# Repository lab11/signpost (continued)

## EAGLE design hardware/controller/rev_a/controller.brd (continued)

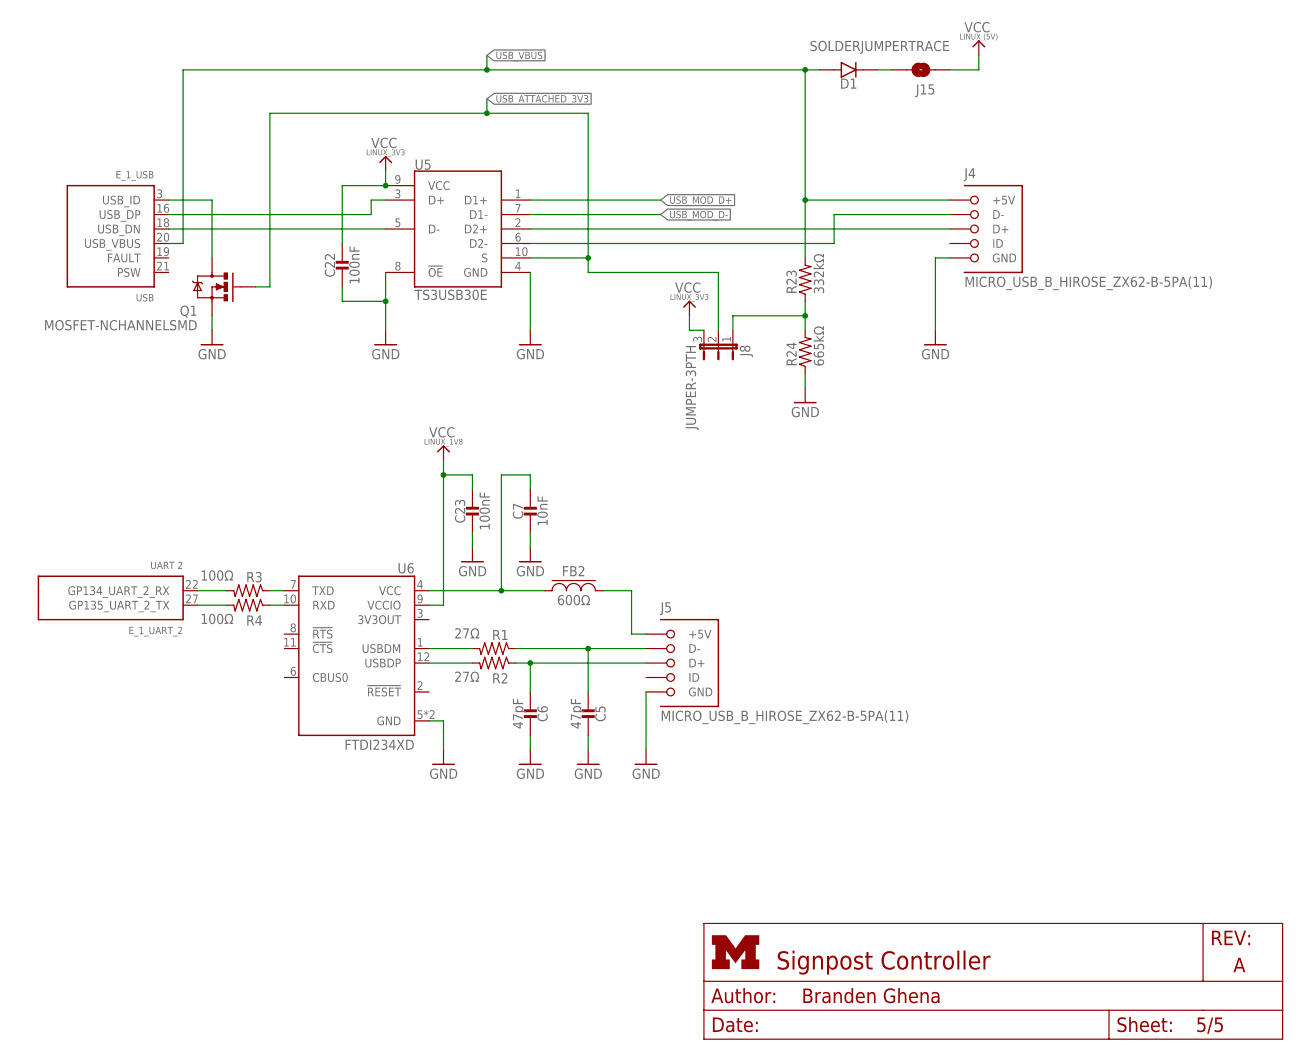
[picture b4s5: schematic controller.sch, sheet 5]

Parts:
C5, C6: 47pF; 0402_CAP; DIGIKEY 490-6241-1-ND
C7: 10nF; 0402_CAP; DIGIKEY 490-6296-1-ND
C22, C23: 100nF; 0402_CAP; DIGIKEY 490-10777-1-ND
D1: DIODE; 0402_DIODE; DIGIKEY P18981CT-ND
E_1: EDISON_CONNECTOR_SEGMENTED; EDISON_DAUGHTER; MOUSER 798-DF40HC3070DS4V51
FB2: 600Ω; 0805_CAP; DIGIKEY 240-2390-1-ND
J4, J5: MICRO_USB_B_HIROSE_ZX62-B-5PA(11); USB_MICRO_B-HIROSE-ZX62-B-5PA(11)
J8: JUMPER-3PTH; 1X03
J15: SOLDERJUMPERTRACE; SJ_2S-TRACE
Q1: MOSFET-NCHANNELSMD; SOT23-3; DIGIKEY SI2312CDS-T1-GE3CT-ND
R1, R2: 27Ω; 0402_RES; DIGIKEY 1276-3907-1-ND
R3, R4: 100Ω; 0402_RES; DIGIKEY 1276-3429-1-ND
R23: 332kΩ; 0402_RES; DIGIKEY 1276-4245-1-ND
R24: 665kΩ; 0402_RES; DIGIKEY 1276-4275-1-ND
U5: TS3USB30E; UQFN-10
U6: FTDI234XD; DFN-12/3MM

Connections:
D+: C6.1, J5.3 (D+), R2.1
D-: C5.1, J5.2 (D-), R1.1
EDISON_UART_RX: E_1.22 (GP134_UART_2_RX), R3.2
EDISON_UART_TX: E_1.27 (GP135_UART_2_TX), R4.2
GND: C5.2, C6.2, C7.2, C22.2, C23.2, J4.5 (GND), J5.5 (GND), Q1.2 (S), R24.1, U5.4 (GND), U5.8 (!OE), U6.5 (GND), U6.13 (GND); also elsewhere on the board
unnamed: R1.2, U6.1 (USBDM)
unnamed: R2.2, U6.12 (USBDP)
unnamed: J4.2 (D-), U5.6 (D2-)
unnamed: J4.3 (D+), U5.2 (D2+)
unnamed: FB2.P$2, J5.1 (+5V)
unnamed: D1.CATHODE, J15.2
unnamed: J8.1, R23.1, R24.2
unnamed: R3.1, U6.7 (TXD)
unnamed: R4.1, U6.10 (RXD)
unnamed: C7.1, FB2.P$1, U6.4 (VCC)
unnamed: E_1.3 (USB_ID), Q1.3 (D)
USB_ATTACHED_3V3: J8.2, Q1.1 (G), U5.10 (S)
USB_D+: E_1.16 (USB_DP), U5.3 (D+)
USB_D-: E_1.18 (USB_DN), U5.5 (D-)
USB_MOD_D+: U5.1 (D1+); also elsewhere on the board
USB_MOD_D-: U5.7 (D1-); also elsewhere on the board
USB_VBUS: D1.ANODE, E_1.20 (USB_VBUS), J4.1 (+5V), R23.2
VCC_LINUX: J15.1; also elsewhere on the board
VCC_LINUX_1V8: C23.1, U6.9 (VCCIO); also elsewhere on the board
VCC_LINUX_3V3: C22.1, J8.3, U5.9 (VCC); also elsewhere on the board

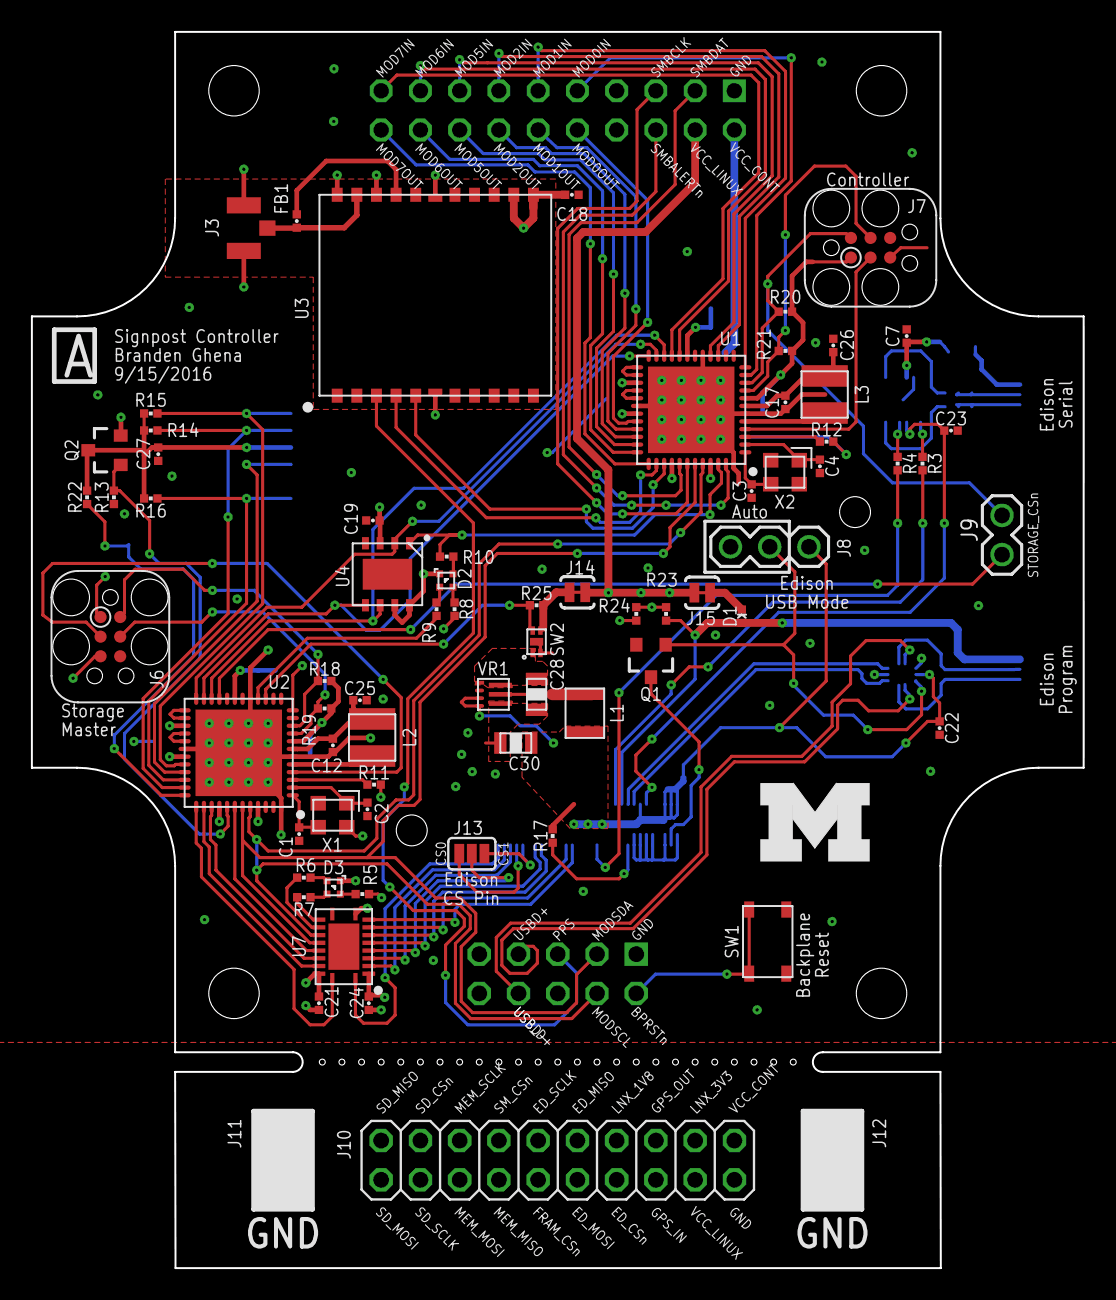
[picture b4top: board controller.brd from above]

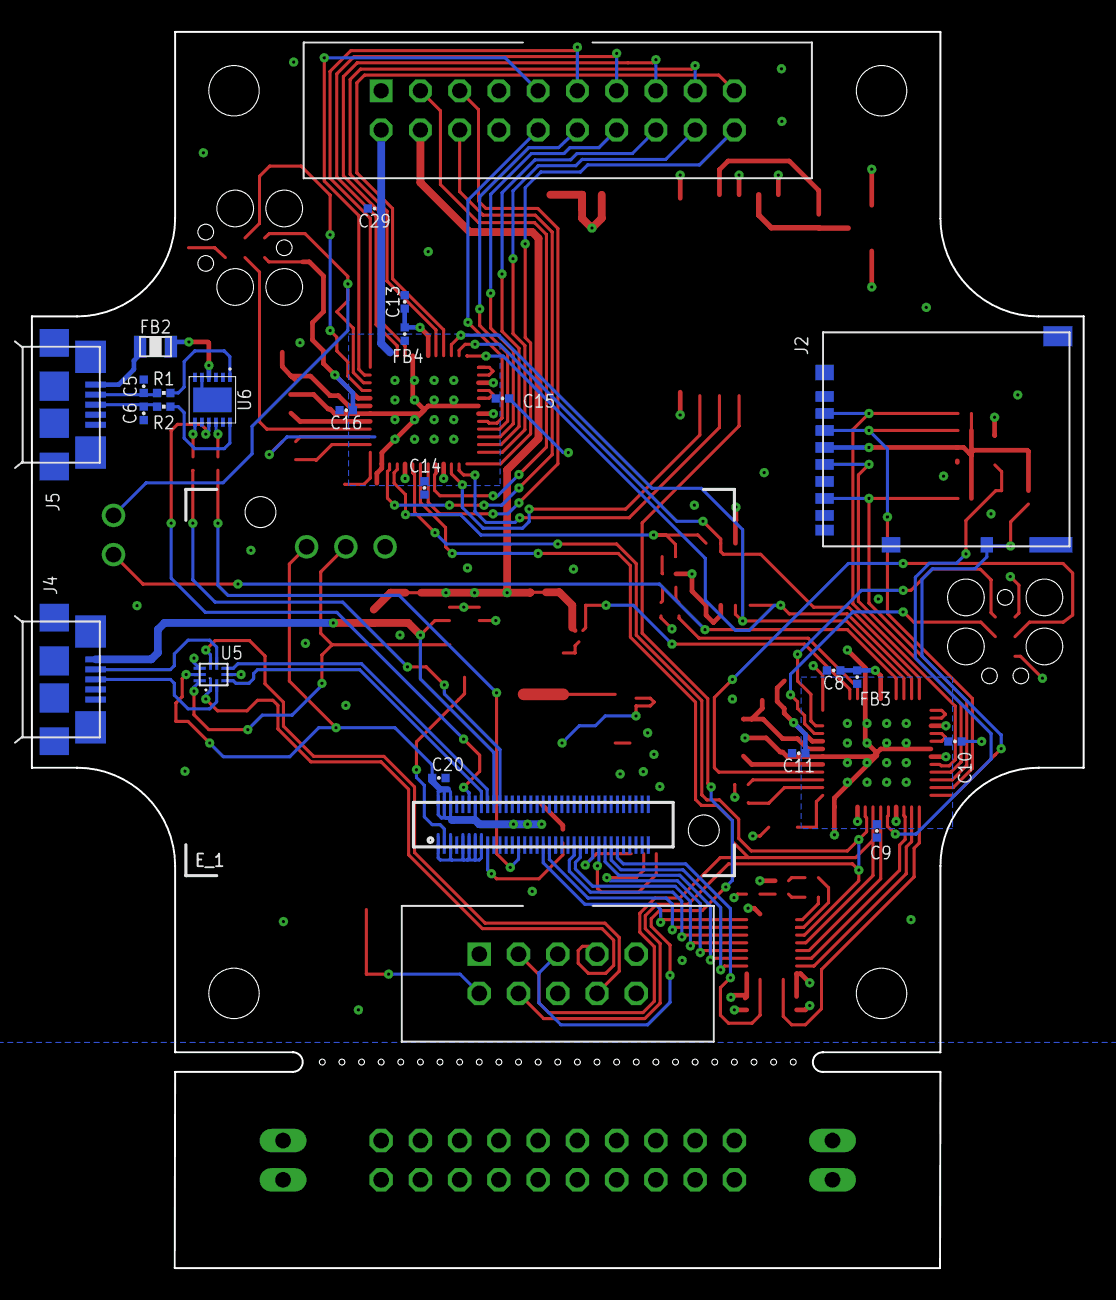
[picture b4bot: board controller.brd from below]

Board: 4 copper layers, 68.1 x 80.0 mm, 96 parts (23 on the bottom side), 111 nets.

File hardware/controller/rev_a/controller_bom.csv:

"Qty";"Value";"Device";"Package";"Parts";"Description";"AMAZON";"DIGIKEY";"MOUSER";"NEWARK";
"1";"";"JUMPER-2PTH";"1X02";"J9";"Jumper";"";"";"";"";
"2";"";"PINHD-1X2";"1X02";"J11, J12";"PIN HEADER";"";"";"";"";
"1";"";"PINHD-2X10";"2X10";"J10";"PIN HEADER";"";"";"";"";
"1";"";"SOLDERJUMPER_2WAYPASTE2&3";"SJ_3_PASTE2&3";"J13";"Solder Jumper";"";"";"";"";
"1";"0.47uH";"INDUCTORDFE322512C";"DFE322512C";"L1";"A very specific inductor";"";"";"81-1277AS-H-R47MP2";"";
"2";"1.5kΩ";"FERRITE_BEAD0402";"0402_CAP";"FB3, FB4";"";"";"490-5216-1-ND";"";"";
"5";"100kΩ";"RESISTOR0402_RES";"0402_RES";"R18, R19, R20, R21, R22";"Resistor";"";"1276-3432-1-ND";"";"";
"17";"100nF";"CAPACITOR0402_CAP";"0402_CAP";"C8, C9, C10, C11, C12, C13, C14, C15, C16, C17, C18, C19, C20, C21, C22, C23, C24";"0402 Capacitor";"";"490-10777-1-ND";"";"";
"2";"100Ω";"RESISTOR0402_RES";"0402_RES";"R3, R4";"Resistor";"";"1276-3429-1-ND";"";"";
"7";"10kΩ";"RESISTOR0402_RES";"0402_RES";"R11, R12, R13, R14, R15, R16, R17";"Resistor";"";"1276-3431-1-ND";"";"";
"1";"10nF";"CAPACITOR0402_CAP";"0402_CAP";"C7";"0402 Capacitor";"";"490-6296-1-ND";"";"";
"1";"10uF";"CAPACITOR0402_CAP";"0402_CAP";"C29";"0402 Capacitor";"";"490-13811-1-ND";"";"";
"1";"10uF";"CAPACITOR0805_CAP";"0805_CAP";"C28";"0402 Capacitor";"";"490-8316-1-ND";"";"";
"2";"16MHz";"FH1600015";"FHXXX";"X1, X2";"Pericom Type FH 16 MHz 2.5 x 2.0 mm";"";"FH1600015CT-ND";"";"";
"1";"1MΩ";"RESISTOR0402_RES";"0402_RES";"R25";"Resistor";"";"1276-3433-1-ND";"";"";
"6";"1kΩ";"RESISTOR0402_RES";"0402_RES";"R5, R6, R7, R8, R9, R10";"Resistor";"";"1276-3430-1-ND";"";"";
"1";"22uF";"CAPACITOR0805_CAP";"0805_CAP";"C30";"0402 Capacitor";"";"490-1719-1-ND";"";"";
"2";"22uH";"LHQ3NP";"1212";"L2, L3";"LHQ3NP Inductor";"";"490-5350-1-ND";"";"";
"2";"27Ω";"RESISTOR0402_RES";"0402_RES";"R1, R2";"Resistor";"";"1276-3907-1-ND";"";"";
"1";"300Ω";"FERRITE_BEAD0402";"0402_CAP";"FB1";"";"";"ACML-0402-301-TCT-ND";"";"";
"1";"332kΩ";"RESISTOR0402_RES";"0402_RES";"R23";"Resistor";"";"1276-4245-1-ND";"";"";
"3";"4.7uF";"CAPACITOR0402_CAP";"0402_CAP";"C25, C26, C27";"0402 Capacitor";"";"490-13252-1-ND";"";"";
"2";"47pF";"CAPACITOR0402_CAP";"0402_CAP";"C5, C6";"0402 Capacitor";"";"490-6241-1-ND";"";"";
"1";"600Ω";"FERRITE_BEAD0805";"0805_CAP";"FB2";"";"";"240-2390-1-ND";"";"";
"1";"665kΩ";"RESISTOR0402_RES";"0402_RES";"R24";"Resistor";"";"1276-4275-1-ND";"";"";
"4";"8pF";"CAPACITOR0402_CAP";"0402_CAP";"C1, C2, C3, C4";"0402 Capacitor";"";"490-8230-1-ND";"";"";
"1";"DIODE";"DIODE";"0402_DIODE";"D1";"";"";"P18981CT-ND";"";"";
"1";"DM3AT-SF-PEJM5";"DM3AT-SF-PEJM5";"DM3AT-SF-PEJM5";"J2";"CONN MICRO SD R/A PUSH-PUSH SMD";"";"HR1964CT-ND";"";"";
"1";"EDISON_CONNECTOR_SEGMENTED";"EDISON_CONNECTOR_SEGMENTED";"EDISON_DAUGHTER";"E_1";"";"B00PTVSS4A";"";"798-DF40HC3070DS4V51";"";
"1";"FM25CLXXB-DG";"FM25CLXXB-DG";"TDFN-8";"U4";"Cypress FRAM";"";"FM25CL64B-DGRA-ND";"";"";
"1";"FTDI234XD";"FTDI234XD";"DFN-12/3MM";"U6";"FTDI234XD USB to UART Bridge in 3x3 DFN Package";"";"768-1178-1-ND";"895-FT234XD-R";"53X3171";
"1";"JUMPER-3PTH";"JUMPER-3PTH";"1X03";"J8";"";"";"";"";"";
"2";"MICRO_USB_B_HIROSE_ZX62-B-5PA(11)";"MICRO_USB_B_HIROSE_ZX62-B-5PA(11)";"USB_MICRO_B-HIROSE-ZX62-B-5PA(11)";"J4, J5";"Connector Receptacle USB - micro B 2.0 5 Position Surface Mount, Right Angle, Horizontal";"";"H11634CT-ND";"798-ZX62-B-5PA11";"86P8793";
"1";"MODULE_CONTROLLER";"MODULE_CONTROLLER";"MODULE_CONTROLLER";"J1";"Controller module for signpost";"";"S9172-ND , S9169-ND";"";"";
"1";"MOSFET-NCHANNELSMD";"MOSFET-NCHANNELSMD";"SOT23-3";"Q1";"Generic NMOS footprint";"";"SI2312CDS-T1-GE3CT-ND";"";"";
"1";"NX3008PBK";"NX3008PBK";"SOT23-3";"Q2";"MOSFET - P Channel";"";"568-10499-1-ND";"771-NX3008PBK,215";"74T4665";
"1";"PTS810SJ";"PTS810SJ";"PTS810SJ";"SW1";"PTS810SJ Push Button Switch";"";"CKN10504CT-ND";"";"";
"1";"RXM-GPS-RM-T";"RXM-GPS-RM-T";"RXM-GPS-RM-T";"U3";"The RM Series GPS receiver module is a";"";"RXM-GPS-RM-TCT-ND";"";"";
"2";"SAM4LC8AA";"SAM4LC8AA";"QFN-48-7MM";"U1, U2";"Atmel SAM4L microcontroller. ARM Cortex M4 with 512 KB Flash and 64 KB RAM";"";"ATSAM4LC8AA-MU-ND";"";"";
"1";"SIP3240X";"SIP3240X";"TDFN4";"SW2";"High power (2.4 A) high-side switch";"";"SIP32402ADNP-T1GE4CT-ND";"";"";
"2";"SML-LX0404SIUPGUSB";"SML-LX0404SIUPGUSB";"1MM_SQ_4PAD";"D2, D3";"1mm^2 RGB LED";"";"67-2125-1-ND";"";"";
"2";"SOLDERJUMPERTRACE";"SOLDERJUMPERTRACE";"SJ_2S-TRACE";"J14, J15";"Solder Jumper";"";"";"";"";
"2";"TC2030-JLINK-L";"TC2030-JLINK-L";"TC2030-IDC";"J6, J7";"";"";"";"";"";
"1";"TPS62086";"TPS62086";"RLT0007A";"VR1";"Buck Switching Regulator IC Positive Fixed 3.3V 1 Output 3A 7-VFDFN";"";"296-40831-1-ND";"";"";
"1";"TS3USB30E";"TS3USB30E";"UQFN-10";"U5";"USB Mux with OE control and ESD";"";"296-24684-1-ND";"";"";
"1";"TXS0108EVQFN20";"TXS0108EVQFN20";"R-PVQFN-N20";"U7";"TXS0108E 8-Bit Bi-directional Voltage Translator";"";"296-24806-1-ND";"";"";
"1";"U.FL-R-SMT";"U.FL-R-SMT";"U.FL_SMT";"J3";"U.FL-R-SMT Antenna Connector";"";"H122041-ND";"";"";
"1";"UMICH_SOLID_MEDIUM";"UMICH_SOLID_MEDIUM";"UMICH_SOLID_200MIL";"LOGO1";"";"";"";"";"";
